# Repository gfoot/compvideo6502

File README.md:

# Composite/component video controller for homebrew 6502 computers

<table>
  <tr><td rowspan="2"></td><td></td></tr>
  <tr><td></td></tr>
</table>

This is my second iteration video output circuit for homebrew 6502 computers.  It's designed to work in a way that's fairly close to
how early 80s microcomputers tended to work, which means RAM shared between CPU and video controller, as this tends to provide the
fastest possible access for the CPU to the video memory.

In this second iteration, the main change from V1 is that the timings are easily configurable, allowing it to support NTSC as well
as PAL with just a few jumper changes, as well as non-standard sync timings if you want to experiment; and the image placement and
size is also easily configurable.

You can also use interlacing to double the vertical resolution to 512 pixels, and if you swap the clock crystal and adjust some
other timings, you can double the horizontal resolution as well.

More involved, higher clock frequencies and maybe more counters would also allow HD resolutions such as 720p and 1080i, though I
haven't tried those yet, and VGA if you also change the output layer to output plain RGB.

The limiting factor at these higher resolutions becomes memory - 384x256x2 already uses nearly half of the RAM.  I'm considering
addressing this through a banking scheme in an upcoming V3.

# Project contents

This project contains:
* Full KiCad schematics for the new design (<a href="images/compvideo6502_schematic.pdf">also available in PDF format</a>)
* A "PCB" layout that represents how you could build this on an array of five breadboards

This includes the 6502, RAM, ROM, oscillator, reset circuit, and address decoding circuits, along 
with the video controller.  If you're already happy with the way you're doing those in an existing system then you could mostly 
keep your old design instead, but the RAM and clock need to be integrated here, in order to be shared with the video controller.

# Next steps and expansion ideas

There are a few things I plan to do next, and I'm not sure what the order will be.  Feedback/contributions welcome - let me know 
if you try these or have other ideas!

* Upload some OS code - I have the code from my previous iteration which should work pretty well
* Document and explain it, maybe make a step-by-step build-and-test guide, video tutorial, or something like that
* Make some games for it!  That was the whole point really, having a video output circuit that's fast enough to support 
the kinds of game I grew up playing
* Colour output - using component video, pretty simple to add
* Higher resolutions?  Doubling the horizontal resolution is possible with the right pixel frequency (13.5MHz instead
of 16MHz) - and doubling the vertical resolution also works fine through interlacing.  Component video can also go up to 1080i I 
think, but can't find good specs on the sync frequencies for that.
* VGA output?  It's fairly similar, just higher frequency - but may be possible by swapping the crystal and adjusting the timings.  
It's why I wanted to make this more configurable than my first one.
* Planar video memory, as used on EGA and VGA graphics cards on PCs - I've always found it an interesting architecture, and it 
seems like a good way to implement colour output without needing faster memory
* Software control over the timing registers would be very neat and not very hard to do

# Caveats

The output impedance isn't exactly what it's meant to be, but it's close enough I think.

The 16MHz base frequency is what the BBC Micro used back in the day, but I think in the digital age the standard pixel sampling 
frequency for SDTV is 13.5MHz.  As a result, on an LCD display you get blurring and moire effects at 8MHz; and at 16MHz you lose 
most of the pixel detail completely.  I think with a 13.5MHz base frequency the picture would be sharper overall.

My first iteration output correct pre- and post-vsync equalization pulses, and serrations during the vsync; I left that out this 
time around as it doesn't seem to be necessary these days.  Maybe I'm missing something though.  As far as I can tell chips like 
the 6845 never supported this anyway - at least it's not mentioned in the datasheets.  So I'm guessing that since at least the 
1980s nobody has bothered with them.

I haven't worked out interlacing yet.  Websites say that you can turn it off with the right combination of sync pulses, but my TV
always says it's interlaced, so either I'm doing it wrong, or the TV just never says "576p" anyway.  The design here is
intentionally fully-interlaced, which might lead to increased vertical resolution in the end.  It should be possible to uninterlace
it with a small change to the sync timings.  Actually I suspect that this is becase composite doesn't support progressive scan -
with component video the non-interlaced mode might work better.

I used a lot of 74HCT40103s in this design - they're incredibly useful, and were fundamental to the simplification and tweakability 
of the timings in this design.  However it seems they might be harder to find online than other chips I tend to use - I had to 
order a second batch, and it was harder to find them this time around.  So maybe it wasn't the best choice...  It's possible to use 
74HCT163s instead, but you'll need more of them as they're only 4-bit counters.

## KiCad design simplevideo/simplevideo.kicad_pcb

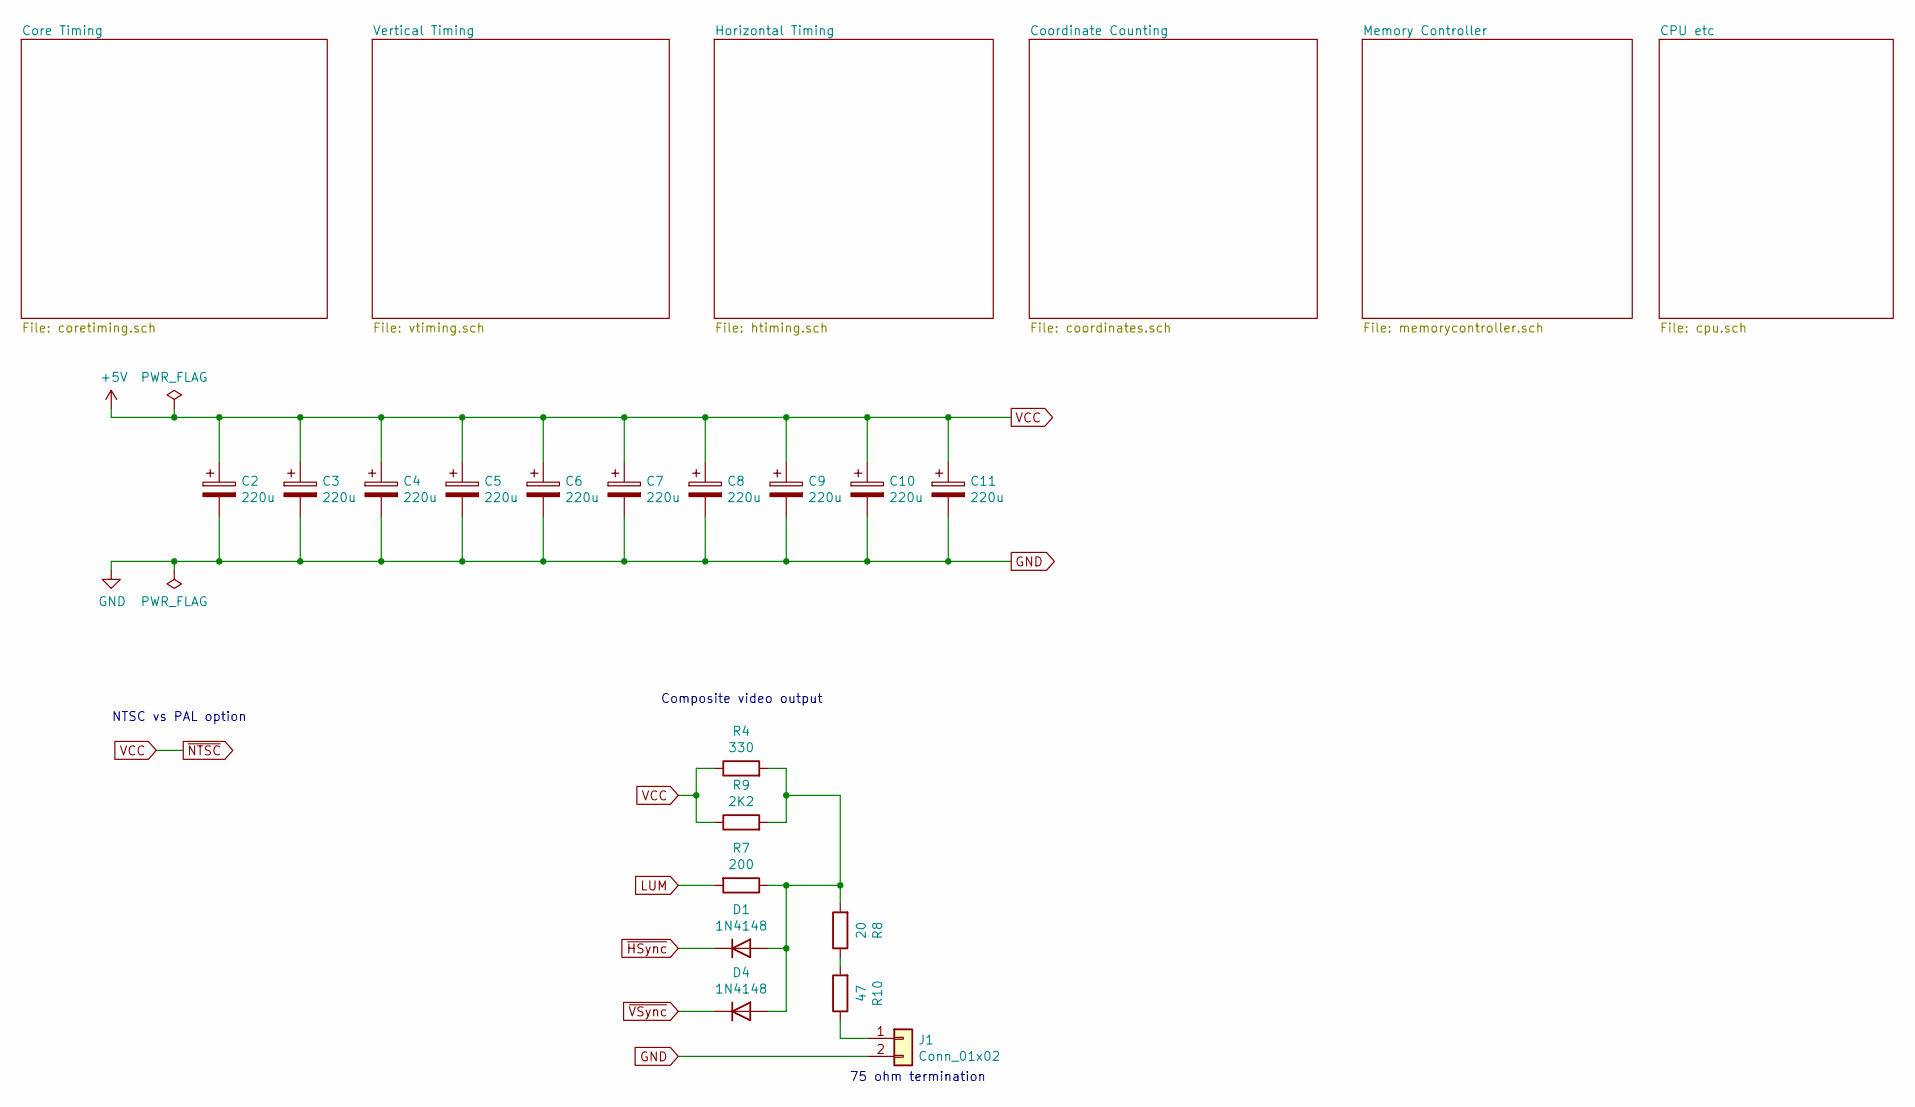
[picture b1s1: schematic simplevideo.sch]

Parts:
C2, C3, C4, C5, C6, C7, C8, C9, C10, C11: 220u; CP_Radial_D5.0mm_P2.50mm
D1, D4: 1N4148; D_DO-34_SOD68_P7.62mm_Horizontal
J1: Conn_01x02; PinHeader_1x02_P2.54mm_Vertical
R4: 330; R_Axial_DIN0204_L3.6mm_D1.6mm_P7.62mm_Horizontal
R7: 200; R_Axial_DIN0204_L3.6mm_D1.6mm_P7.62mm_Horizontal
R8: 20; R_Axial_DIN0204_L3.6mm_D1.6mm_P7.62mm_Horizontal
R9: 2K2; R_Axial_DIN0204_L3.6mm_D1.6mm_P7.62mm_Horizontal
R10: 47; R_Axial_DIN0204_L3.6mm_D1.6mm_P7.62mm_Horizontal

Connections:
GND: C2.2, C3.2, C4.2, C5.2, C6.2, C7.2, C8.2, C9.2, C10.2, C11.2, J1.2; also elsewhere on the board
LUM: R7.2; also elsewhere on the board
unnamed: D1.2 (A), D4.2 (A), R4.2, R7.1, R8.2, R9.2
unnamed: J1.1, R10.1
unnamed: R8.1, R10.2
VCC: C2.1, C3.1, C4.1, C5.1, C6.1, C7.1, C8.1, C9.1, C10.1, C11.1, R4.1, R9.1; also elsewhere on the board
~HSync: D1.1 (K); also elsewhere on the board
~VSync: D4.1 (K); also elsewhere on the board

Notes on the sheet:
NTSC vs PAL option
Composite video output
75 ohm termination

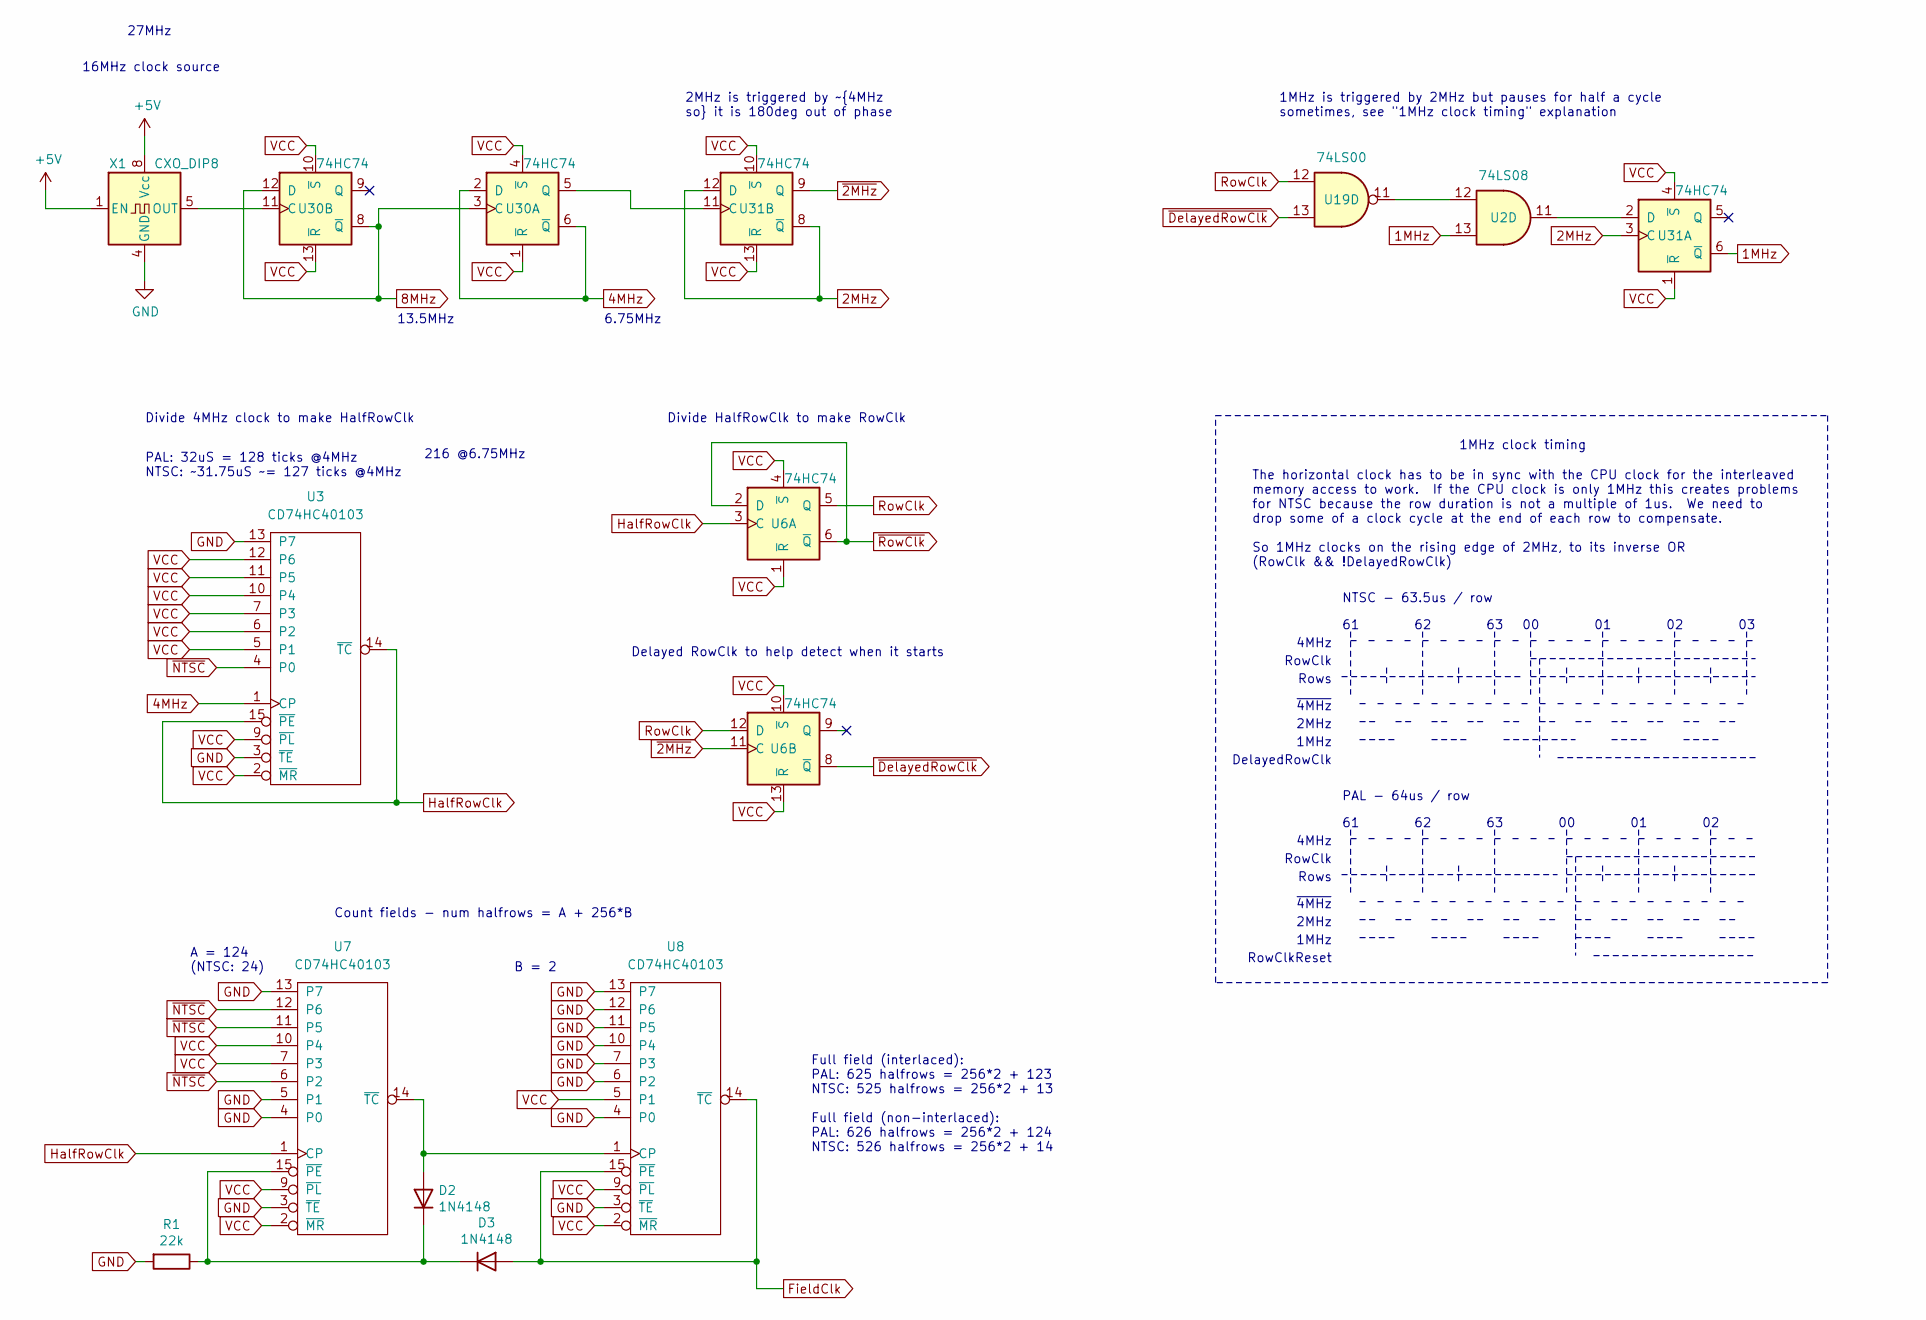
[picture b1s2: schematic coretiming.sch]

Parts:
D2, D3: 1N4148; D_DO-34_SOD68_P7.62mm_Horizontal
R1: 22k; R_Axial_DIN0204_L3.6mm_D1.6mm_P7.62mm_Horizontal
U2: 74LS08; DIP-14_W7.62mm
U3, U7, U8: CD74HC40103; DIP-16_W7.62mm
U6, U30, U31: 74HC74; DIP-14_W7.62mm
U19: 74LS00; DIP-14_W7.62mm
X1: CXO_DIP8; Oscillator_DIP-8

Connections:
1MHz: U2.13, U31.6 (~Q); also elsewhere on the board
2MHz: U31.3 (C), U31.8 (~Q), U31.12 (D)
4MHz: U3.1 (CP), U30.2 (D), U30.6 (~Q); also elsewhere on the board
8MHz: U30.3 (C), U30.8 (~Q), U30.12 (D); also elsewhere on the board
FieldClk: D3.2 (A), U8.14 (~TC), U8.15 (~PE); also elsewhere on the board
GND: R1.2, U3.3 (~TE), U3.8 (GND), U3.13 (P7), U7.3 (~TE), U7.4 (P0), U7.5 (P1), U7.8 (GND), U7.13 (P7), U8.3 (~TE), U8.4 (P0), U8.6 (P2), U8.7 (P3), U8.8 (GND), U8.10 (P4), U8.11 (P5), U8.12 (P6), U8.13 (P7), X1.4 (GND); also elsewhere on the board
HalfRowClk: U3.14 (~TC), U3.15 (~PE), U6.3 (C), U7.1 (CP); also elsewhere on the board
unnamed: D2.1 (K), D3.1 (K), R1.1, U7.15 (~PE)
unnamed: D2.2 (A), U7.14 (~TC), U8.1 (CP)
unnamed: U2.11, U31.2 (D)
unnamed: U2.12, U19.11
unnamed: U30.5 (Q), U31.11 (C)
unnamed: U30.11 (C), X1.5 (OUT)
RowClk: U6.5 (Q), U6.12 (D), U19.12; also elsewhere on the board
VCC: U3.2 (~MR), U3.4 (P0), U3.5 (P1), U3.6 (P2), U3.7 (P3), U3.9 (~PL), U3.10 (P4), U3.11 (P5), U3.12 (P6), U3.16 (VCC), U6.1 (~R), U6.4 (~S), U6.10 (~S), U6.13 (~R), U7.2 (~MR), U7.6 (P2), U7.7 (P3), U7.9 (~PL), U7.10 (P4), U7.11 (P5), U7.12 (P6), U7.16 (VCC), U8.2 (~MR), U8.5 (P1), U8.9 (~PL), U8.16 (VCC), U30.1 (~R), U30.4 (~S), U30.10 (~S), U30.13 (~R), U31.1 (~R), U31.4 (~S), U31.10 (~S), U31.13 (~R), X1.1 (EN), X1.8 (Vcc); also elsewhere on the board
~2MHz: U6.11 (C), U31.9 (Q); also elsewhere on the board
~DelayedRowClk: U6.8 (~Q), U19.13
~RowClk: U6.2 (D), U6.6 (~Q)

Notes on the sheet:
PAL: 32uS = 128 ticks @4MHz NTSC: ~~31.75uS ~~= 127 ticks @4MHz
Divide 4MHz clock to make HalfRowClk
Divide HalfRowClk to make RowClk
Full field (interlaced): PAL: 625 halfrows = 256*2 + 123 NTSC: 525 halfrows = 256*2 + 13 Full field (non-interlaced): PAL: 626 halfrows = 256*2 + 124 NTSC: 526 halfrows = 256*2 + 14
16MHz clock source
Count fields - num halfrows = A + 256*B
A = 124 (NTSC: 24)
B = 2
The horizontal clock has to be in sync with the CPU clock for the interleaved memory access to work. If the CPU clock is only 1MHz this creates problems for NTSC because the row duration is not a multiple of 1us. We need to drop some of a clock cycle at the end of each row to compensate. So 1MHz cl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
1MHz
2MHz
~4MHz
Rows
RowClk
4MHz
RowClkReset
NTSC - 63.5us / row
PAL - 64us / row
DelayedRowClk
1MHz clock timing
2MHz is triggered by ~4MHz so it is 180deg out of phase
1MHz is triggered by 2MHz but pauses for half a cycle sometimes, see "1MHz clock timing" explanation
Delayed RowClk to help detect when it starts
27MHz
13.5MHz
6.75MHz
216 @6.75MHz

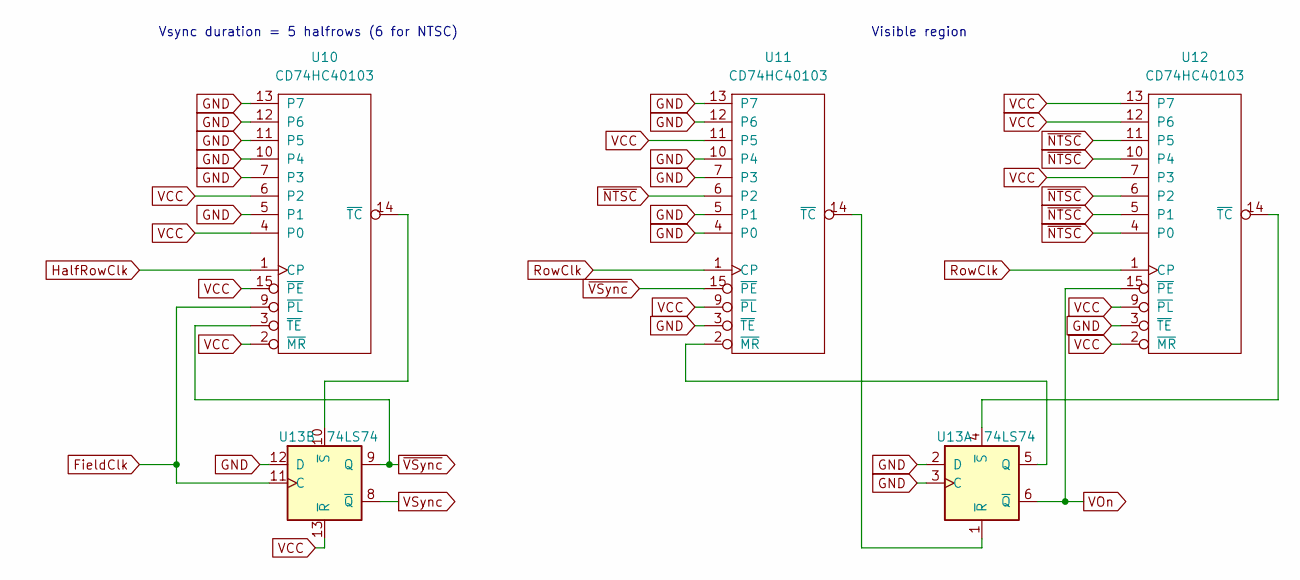
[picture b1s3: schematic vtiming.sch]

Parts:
U10, U11, U12: CD74HC40103; DIP-16_W7.62mm
U13: 74LS74; DIP-14_W7.62mm

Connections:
FieldClk: U10.9 (~PL), U13.11 (C); also elsewhere on the board
GND: U10.5 (P1), U10.7 (P3), U10.8 (GND), U10.10 (P4), U10.11 (P5), U10.12 (P6), U10.13 (P7), U11.3 (~TE), U11.4 (P0), U11.5 (P1), U11.7 (P3), U11.8 (GND), U11.10 (P4), U11.12 (P6), U11.13 (P7), U12.3 (~TE), U12.8 (GND), U13.2 (D), U13.3 (C), U13.12 (D); also elsewhere on the board
HalfRowClk: U10.1 (CP); also elsewhere on the board
unnamed: U10.14 (~TC), U13.10 (~S)
unnamed: U11.2 (~MR), U13.5 (Q)
unnamed: U11.14 (~TC), U13.1 (~R)
unnamed: U12.14 (~TC), U13.4 (~S)
RowClk: U11.1 (CP), U12.1 (CP); also elsewhere on the board
VCC: U10.2 (~MR), U10.4 (P0), U10.6 (P2), U10.15 (~PE), U10.16 (VCC), U11.6 (P2), U11.9 (~PL), U11.11 (P5), U11.16 (VCC), U12.2 (~MR), U12.4 (P0), U12.5 (P1), U12.6 (P2), U12.7 (P3), U12.9 (~PL), U12.10 (P4), U12.11 (P5), U12.12 (P6), U12.13 (P7), U12.16 (VCC), U13.13 (~R); also elsewhere on the board
VOn: U12.15 (~PE), U13.6 (~Q); also elsewhere on the board
VSync: U13.8 (~Q); also elsewhere on the board
~VSync: U10.3 (~TE), U11.15 (~PE), U13.9 (Q); also elsewhere on the board

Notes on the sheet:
Vsync duration = 5 halfrows (6 for NTSC)
Visible region

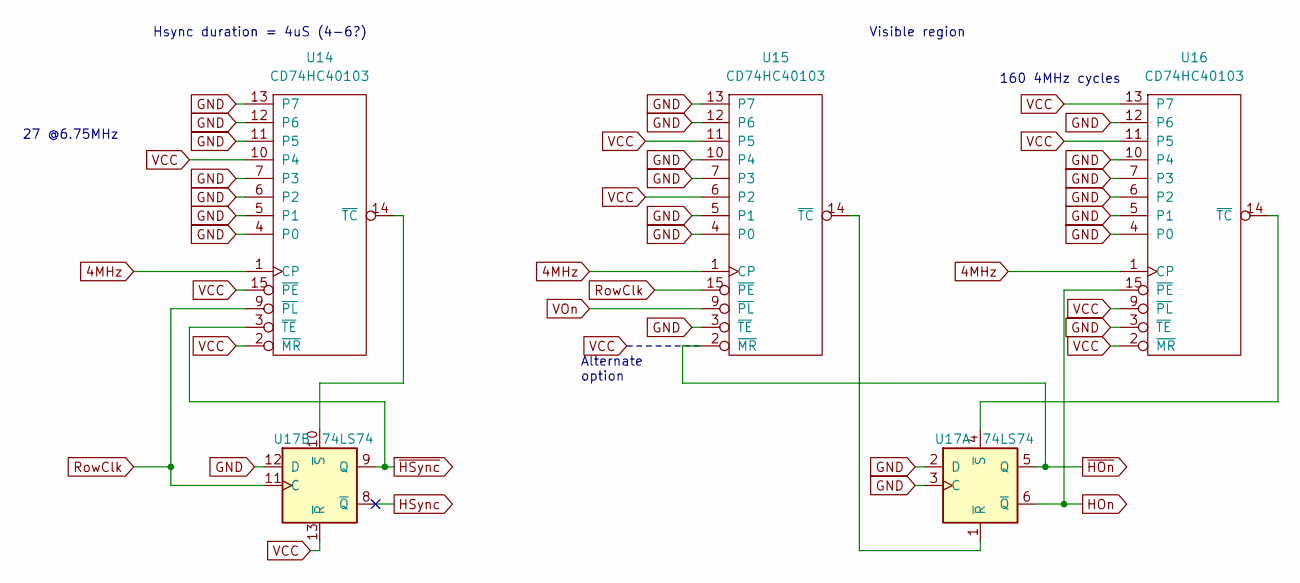
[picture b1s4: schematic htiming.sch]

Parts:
U14, U15, U16: CD74HC40103; DIP-16_W7.62mm
U17: 74LS74; DIP-14_W7.62mm

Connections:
4MHz: U14.1 (CP), U15.1 (CP), U16.1 (CP); also elsewhere on the board
GND: U14.4 (P0), U14.5 (P1), U14.6 (P2), U14.7 (P3), U14.8 (GND), U14.11 (P5), U14.12 (P6), U14.13 (P7), U15.3 (~TE), U15.4 (P0), U15.5 (P1), U15.7 (P3), U15.8 (GND), U15.10 (P4), U15.12 (P6), U15.13 (P7), U16.3 (~TE), U16.4 (P0), U16.5 (P1), U16.6 (P2), U16.7 (P3), U16.8 (GND), U16.10 (P4), U16.12 (P6), U17.2 (D), U17.3 (C), U17.12 (D); also elsewhere on the board
HOn: U16.15 (~PE), U17.6 (~Q); also elsewhere on the board
HSync: U17.8 (~Q)
unnamed: U14.14 (~TC), U17.10 (~S)
unnamed: U15.14 (~TC), U17.1 (~R)
unnamed: U16.14 (~TC), U17.4 (~S)
RowClk: U14.9 (~PL), U15.15 (~PE), U17.11 (C); also elsewhere on the board
VCC: U14.2 (~MR), U14.10 (P4), U14.15 (~PE), U14.16 (VCC), U15.6 (P2), U15.11 (P5), U15.16 (VCC), U16.2 (~MR), U16.9 (~PL), U16.11 (P5), U16.13 (P7), U16.16 (VCC), U17.13 (~R); also elsewhere on the board
VOn: U15.9 (~PL); also elsewhere on the board
~HOn: U15.2 (~MR), U17.5 (Q); also elsewhere on the board
~HSync: U14.3 (~TE), U17.9 (Q); also elsewhere on the board

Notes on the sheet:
Hsync duration = 4uS (4-6?)
Visible region
Alternate option
27 @6.75MHz
160 4MHz cycles

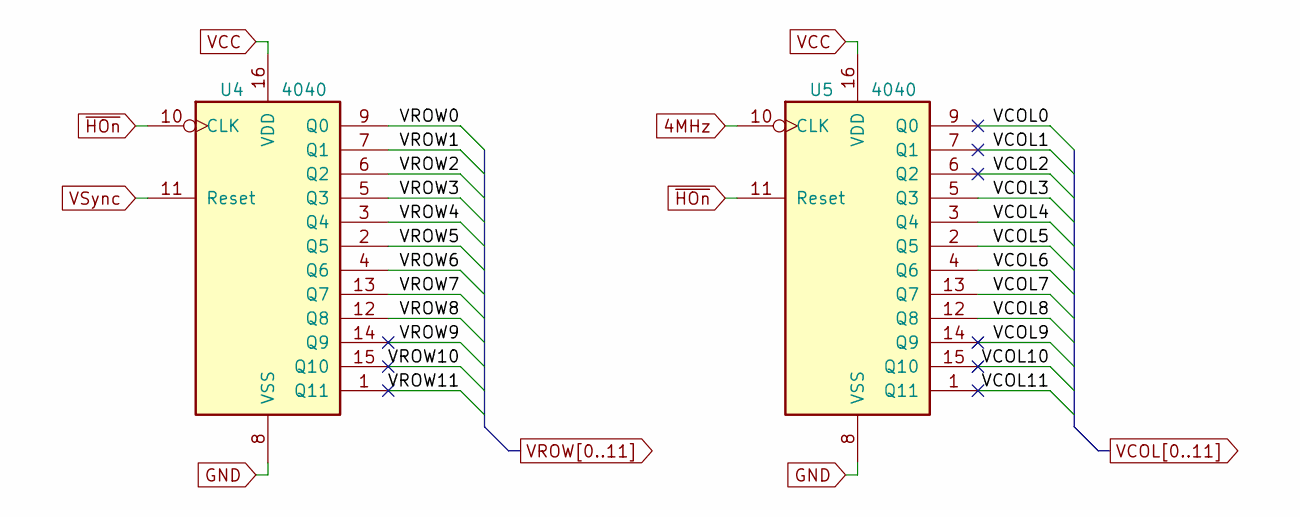
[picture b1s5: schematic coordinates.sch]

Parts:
U4, U5: 4040; DIP-16_W7.62mm

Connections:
4MHz: U5.10 (CLK); also elsewhere on the board
GND: U4.8 (VSS), U5.8 (VSS); also elsewhere on the board
VCC: U4.16 (VDD), U5.16 (VDD); also elsewhere on the board
VCOL0: U5.9 (Q0)
VCOL1: U5.7 (Q1)
VCOL2: U5.6 (Q2)
VCOL3: U5.5 (Q3); also elsewhere on the board
VCOL4: U5.3 (Q4); also elsewhere on the board
VCOL5: U5.2 (Q5); also elsewhere on the board
VCOL6: U5.4 (Q6); also elsewhere on the board
VCOL7: U5.13 (Q7); also elsewhere on the board
VCOL8: U5.12 (Q8); also elsewhere on the board
VCOL9: U5.14 (Q9)
VCOL10: U5.15 (Q10)
VCOL11: U5.1 (Q11)
VROW0: U4.9 (Q0); also elsewhere on the board
VROW1: U4.7 (Q1); also elsewhere on the board
VROW2: U4.6 (Q2); also elsewhere on the board
VROW3: U4.5 (Q3); also elsewhere on the board
VROW4: U4.3 (Q4); also elsewhere on the board
VROW5: U4.2 (Q5); also elsewhere on the board
VROW6: U4.4 (Q6); also elsewhere on the board
VROW7: U4.13 (Q7); also elsewhere on the board
VROW8: U4.12 (Q8); also elsewhere on the board
VROW9: U4.14 (Q9)
VROW10: U4.15 (Q10)
VROW11: U4.1 (Q11)
VSync: U4.11 (Reset); also elsewhere on the board
~HOn: U4.10 (CLK), U5.11 (Reset); also elsewhere on the board

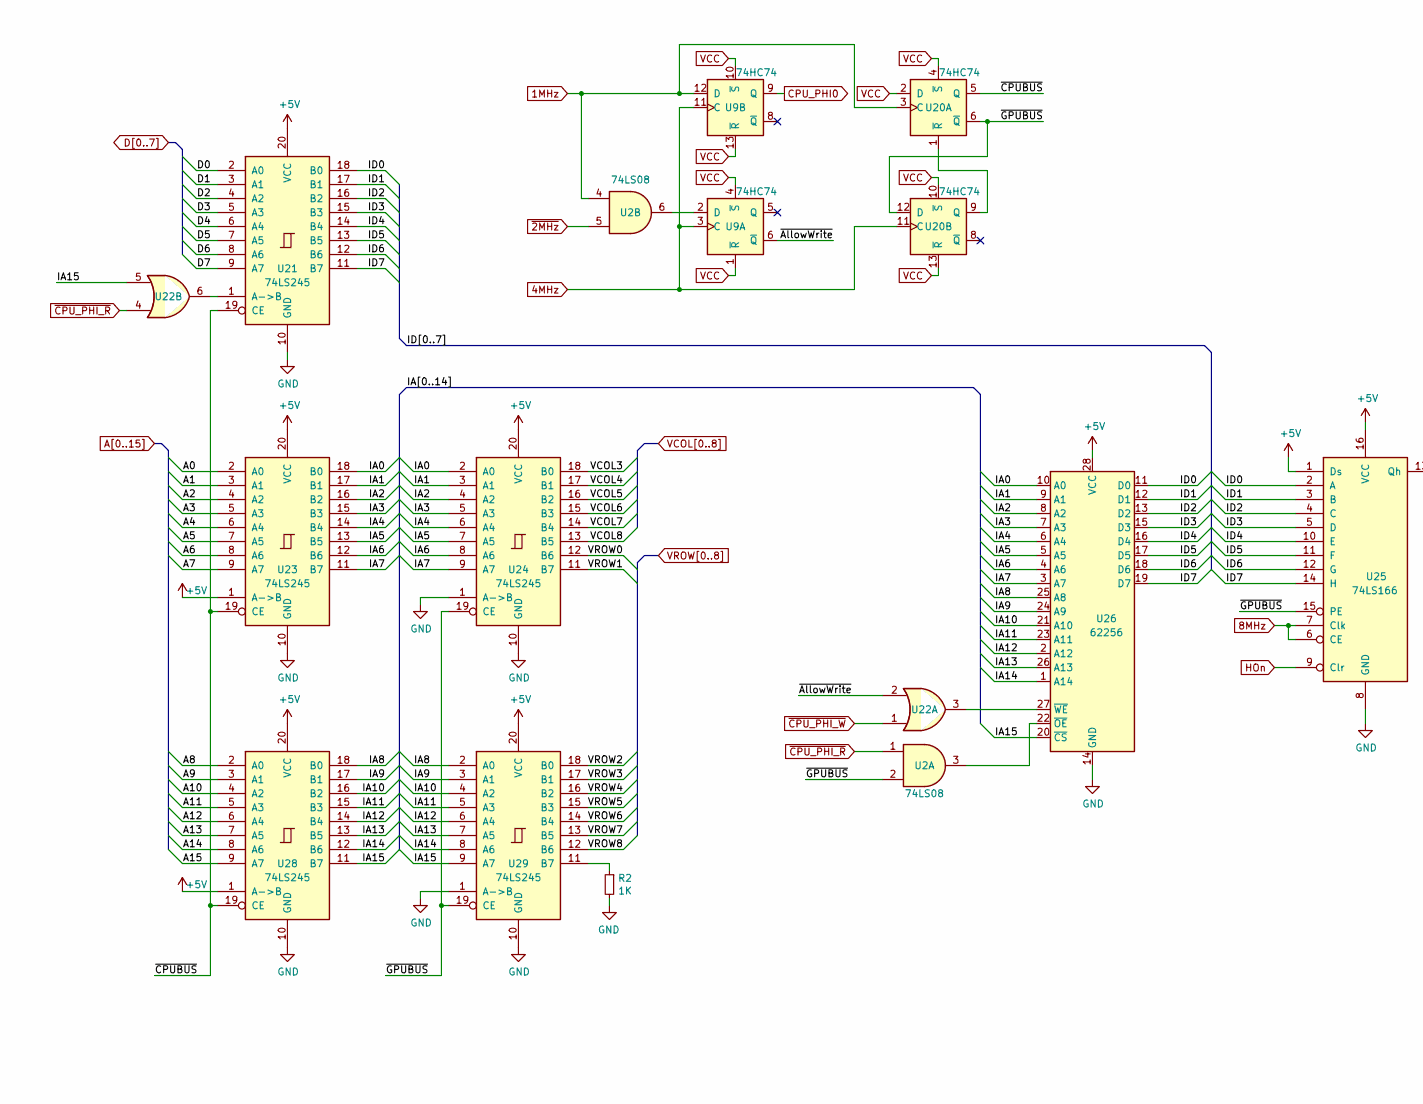
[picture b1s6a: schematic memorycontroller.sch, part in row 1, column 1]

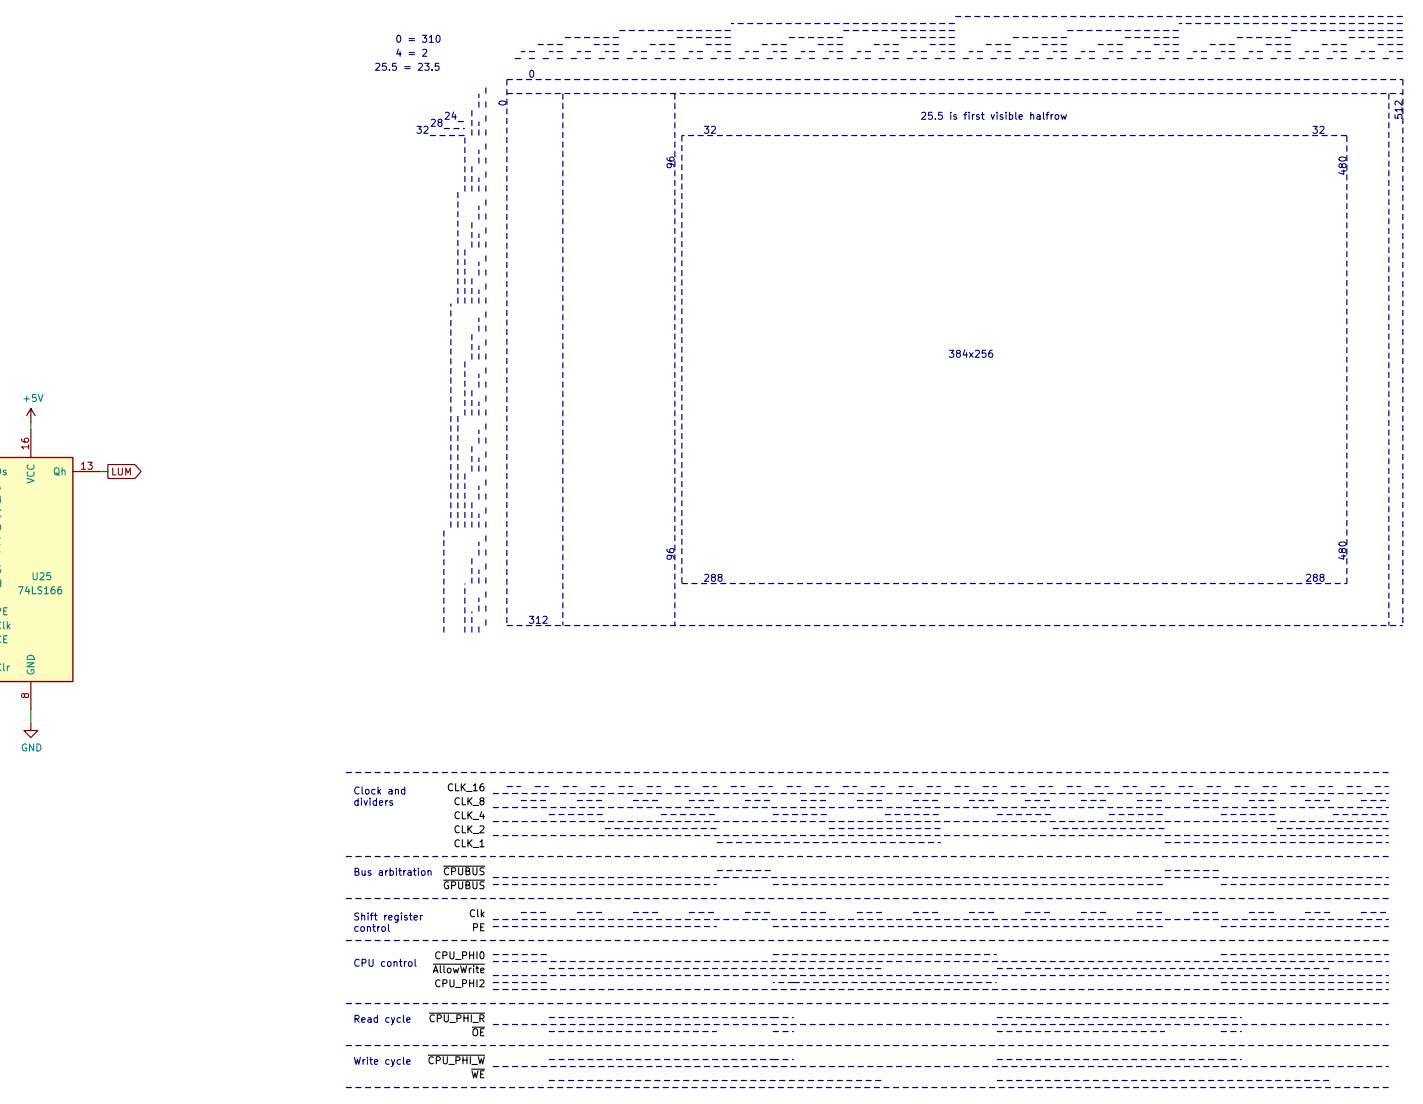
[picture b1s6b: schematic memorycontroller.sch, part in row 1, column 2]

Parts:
R2: 1K; R_Axial_DIN0207_L6.3mm_D2.5mm_P7.62mm_Horizontal
U2: 74LS08; DIP-14_W7.62mm
U9, U20: 74HC74; DIP-14_W7.62mm
U21, U23, U24, U28, U29: 74LS245; DIP-20_W7.62mm
U22: 74LS32; DIP-14_W7.62mm
U25: 74LS166; DIP-16_W7.62mm
U26: 62256; DIP-28_W15.24mm

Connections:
1MHz: U2.4, U9.12 (D), U20.3 (C); also elsewhere on the board
4MHz: U9.3 (C), U9.11 (C), U20.11 (C); also elsewhere on the board
8MHz: U25.6 (CE), U25.7 (Clk); also elsewhere on the board
/Memory Controller/IA0: U23.18 (B0), U24.2 (A0), U26.10 (A0)
/Memory Controller/IA1: U23.17 (B1), U24.3 (A1), U26.9 (A1)
/Memory Controller/IA2: U23.16 (B2), U24.4 (A2), U26.8 (A2)
/Memory Controller/IA3: U23.15 (B3), U24.5 (A3), U26.7 (A3)
/Memory Controller/IA4: U23.14 (B4), U24.6 (A4), U26.6 (A4)
/Memory Controller/IA5: U23.13 (B5), U24.7 (A5), U26.5 (A5)
/Memory Controller/IA6: U23.12 (B6), U24.8 (A6), U26.4 (A6)
/Memory Controller/IA7: U23.11 (B7), U24.9 (A7), U26.3 (A7)
/Memory Controller/IA8: U26.25 (A8), U28.18 (B0), U29.2 (A0)
/Memory Controller/IA9: U26.24 (A9), U28.17 (B1), U29.3 (A1)
/Memory Controller/IA10: U26.21 (A10), U28.16 (B2), U29.4 (A2)
/Memory Controller/IA11: U26.23 (A11), U28.15 (B3), U29.5 (A3)
/Memory Controller/IA12: U26.2 (A12), U28.14 (B4), U29.6 (A4)
/Memory Controller/IA13: U26.26 (A13), U28.13 (B5), U29.7 (A5)
/Memory Controller/IA14: U26.1 (A14), U28.12 (B6), U29.8 (A6)
/Memory Controller/IA15: U22.5, U26.20 (~CS), U28.11 (B7), U29.9 (A7)
/Memory Controller/ID0: U21.18 (B0), U25.2 (A), U26.11 (D0)
/Memory Controller/ID1: U21.17 (B1), U25.3 (B), U26.12 (D1)
/Memory Controller/ID2: U21.16 (B2), U25.4 (C), U26.13 (D2)
/Memory Controller/ID3: U21.15 (B3), U25.5 (D), U26.15 (D3)
/Memory Controller/ID4: U21.14 (B4), U25.10 (E), U26.16 (D4)
/Memory Controller/ID5: U21.13 (B5), U25.11 (F), U26.17 (D5)
/Memory Controller/ID6: U21.12 (B6), U25.12 (G), U26.18 (D6)
/Memory Controller/ID7: U21.11 (B7), U25.14 (H), U26.19 (D7)
/Memory Controller/~AllowWrite: U9.6 (~Q), U22.2
/Memory Controller/~CPUBUS: U20.5 (Q), U21.19 (CE), U23.19 (CE), U28.19 (CE)
/Memory Controller/~GPUBUS: U2.2, U20.6 (~Q), U20.12 (D), U24.19 (CE), U25.15 (PE), U29.19 (CE)
A0: U23.2 (A0); also elsewhere on the board
A1: U23.3 (A1); also elsewhere on the board
A2: U23.4 (A2); also elsewhere on the board
A3: U23.5 (A3); also elsewhere on the board
A4: U23.6 (A4); also elsewhere on the board
A5: U23.7 (A5); also elsewhere on the board
A6: U23.8 (A6); also elsewhere on the board
A7: U23.9 (A7); also elsewhere on the board
A8: U28.2 (A0); also elsewhere on the board
A9: U28.3 (A1); also elsewhere on the board
A10: U28.4 (A2); also elsewhere on the board
A11: U28.5 (A3); also elsewhere on the board
A12: U28.6 (A4); also elsewhere on the board
A13: U28.7 (A5); also elsewhere on the board
A14: U28.8 (A6); also elsewhere on the board
A15: U28.9 (A7); also elsewhere on the board
CPU_PHI0: U9.9 (Q); also elsewhere on the board
D0: U21.2 (A0); also elsewhere on the board
D1: U21.3 (A1); also elsewhere on the board
D2: U21.4 (A2); also elsewhere on the board
D3: U21.5 (A3); also elsewhere on the board
D4: U21.6 (A4); also elsewhere on the board
D5: U21.7 (A5); also elsewhere on the board
D6: U21.8 (A6); also elsewhere on the board
D7: U21.9 (A7); also elsewhere on the board
GND: R2.2, U21.10 (GND), U23.10 (GND), U24.1 (A->B), U24.10 (GND), U25.8 (GND), U26.14 (GND), U28.10 (GND), U29.1 (A->B), U29.10 (GND); also elsewhere on the board
HOn: U25.9 (Clr); also elsewhere on the board
LUM: U25.13 (Qh); also elsewhere on the board
unnamed: R2.1, U29.11 (B7)
unnamed: U2.3, U26.22 (~OE)
unnamed: U2.6, U9.2 (D)
unnamed: U20.1 (~R), U20.9 (Q)
unnamed: U21.1 (A->B), U22.6
unnamed: U22.3, U26.27 (~WE)
VCC: U9.1 (~R), U9.4 (~S), U9.10 (~S), U9.13 (~R), U20.2 (D), U20.4 (~S), U20.10 (~S), U20.13 (~R), U21.20 (VCC), U23.1 (A->B), U23.20 (VCC), U24.20 (VCC), U25.1 (Ds), U25.16 (VCC), U26.28 (VCC), U28.1 (A->B), U28.20 (VCC), U29.20 (VCC); also elsewhere on the board
VCOL3: U24.18 (B0); also elsewhere on the board
VCOL4: U24.17 (B1); also elsewhere on the board
VCOL5: U24.16 (B2); also elsewhere on the board
VCOL6: U24.15 (B3); also elsewhere on the board
VCOL7: U24.14 (B4); also elsewhere on the board
VCOL8: U24.13 (B5); also elsewhere on the board
VROW0: U24.12 (B6); also elsewhere on the board
VROW1: U24.11 (B7); also elsewhere on the board
VROW2: U29.18 (B0); also elsewhere on the board
VROW3: U29.17 (B1); also elsewhere on the board
VROW4: U29.16 (B2); also elsewhere on the board
VROW5: U29.15 (B3); also elsewhere on the board
VROW6: U29.14 (B4); also elsewhere on the board
VROW7: U29.13 (B5); also elsewhere on the board
VROW8: U29.12 (B6); also elsewhere on the board
~2MHz: U2.5; also elsewhere on the board
~CPU_PHI_R: U2.1, U22.4; also elsewhere on the board
~CPU_PHI_W: U22.1; also elsewhere on the board

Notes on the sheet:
512
312
25.5 is first visible halfrow
0 = 310
4 = 2
25.5 = 23.5
480
288
384x256
Shift register control
CPU control
Read cycle
Write cycle
Clock and dividers
Bus arbitration

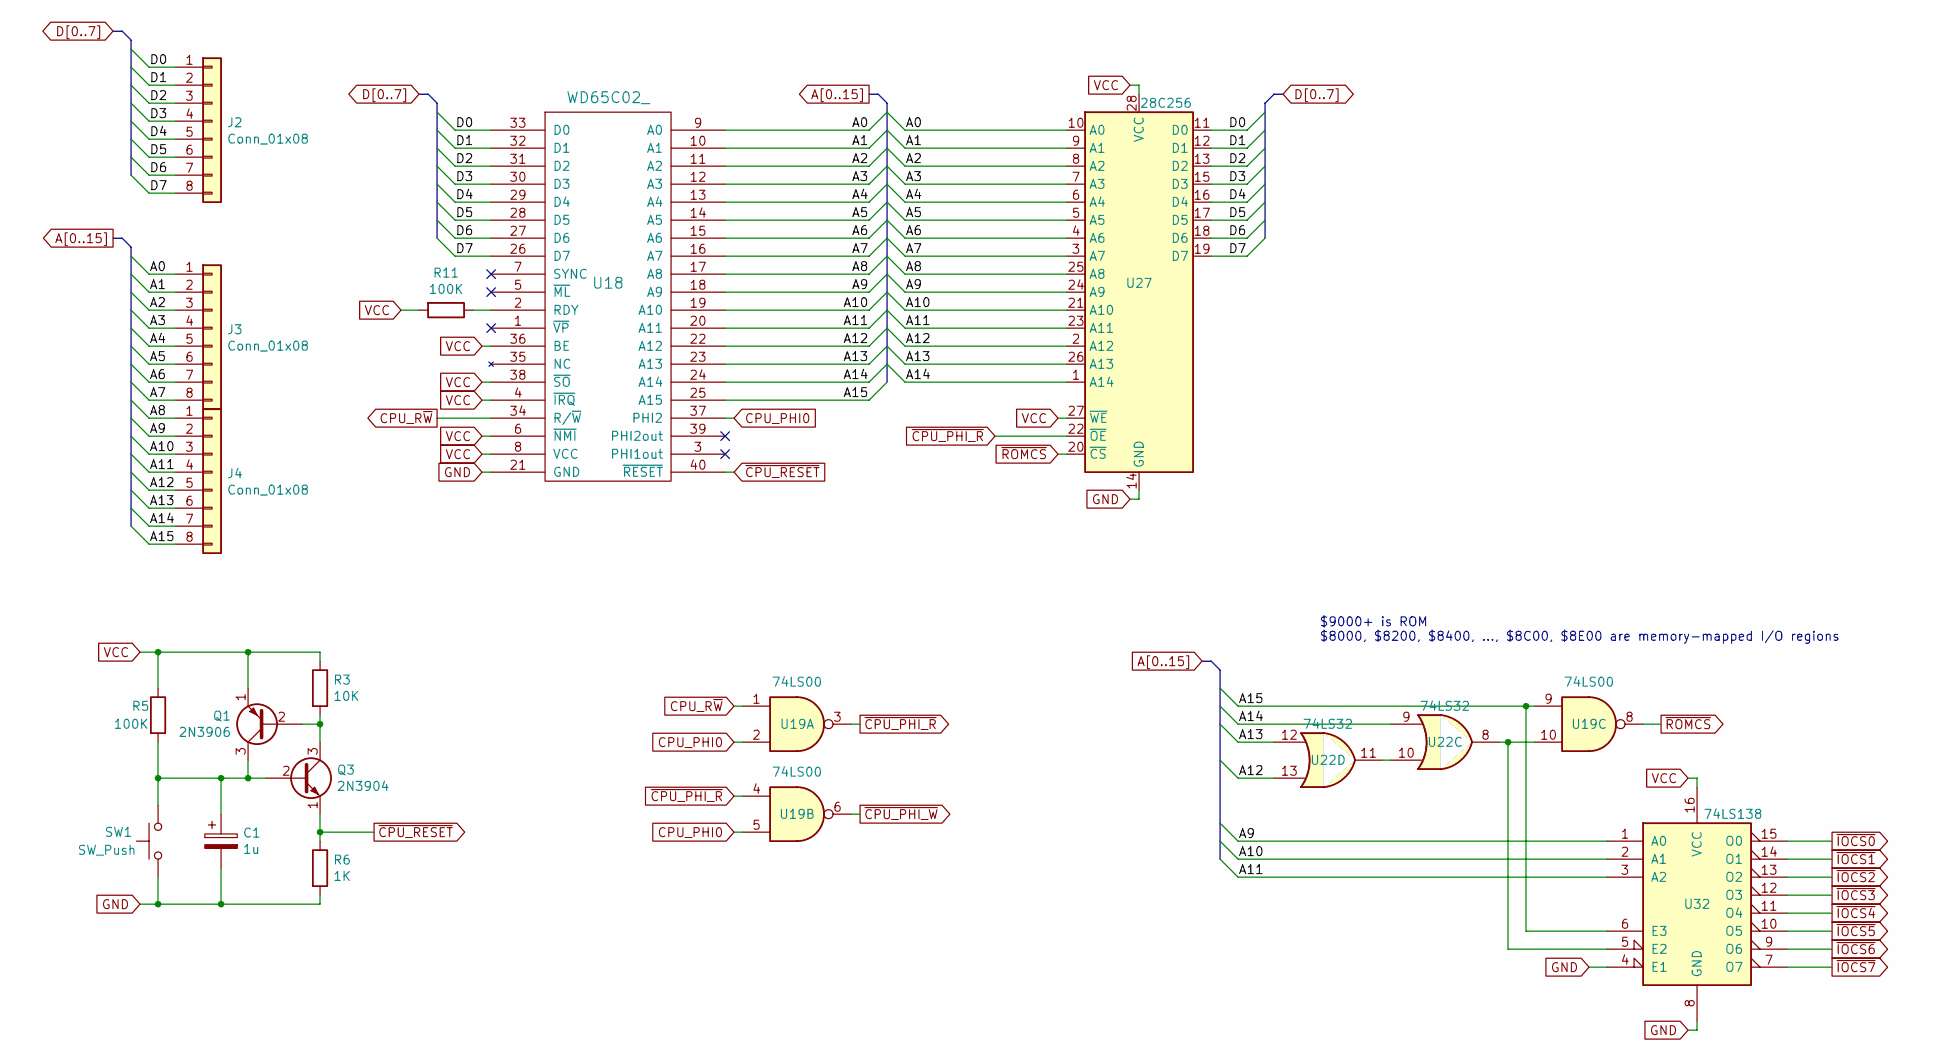
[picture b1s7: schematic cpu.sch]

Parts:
C1: 1u; CP_Radial_D5.0mm_P2.50mm
J2, J3, J4: Conn_01x08; PinHeader_1x08_P2.54mm_Vertical
Q1: 2N3906; TO-92_Inline
Q3: 2N3904; TO-92_Inline
R3: 10K; R_Axial_DIN0207_L6.3mm_D2.5mm_P7.62mm_Horizontal
R5, R11: 100K; R_Axial_DIN0207_L6.3mm_D2.5mm_P7.62mm_Horizontal
R6: 1K; R_Axial_DIN0207_L6.3mm_D2.5mm_P7.62mm_Horizontal
SW1: SW_Push; SW_PUSH_6mm
U18: WD65C02_; DIP-40_W15.24mm
U19: 74LS00; DIP-14_W7.62mm
U22: 74LS32; DIP-14_W7.62mm
U27: 28C256; DIP-28_W15.24mm
U32: 74LS138; DIP-16_W7.62mm

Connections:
A0: J3.1, U18.9 (A0), U27.10 (A0); also elsewhere on the board
A1: J3.2, U18.10 (A1), U27.9 (A1); also elsewhere on the board
A2: J3.3, U18.11 (A2), U27.8 (A2); also elsewhere on the board
A3: J3.4, U18.12 (A3), U27.7 (A3); also elsewhere on the board
A4: J3.5, U18.13 (A4), U27.6 (A4); also elsewhere on the board
A5: J3.6, U18.14 (A5), U27.5 (A5); also elsewhere on the board
A6: J3.7, U18.15 (A6), U27.4 (A6); also elsewhere on the board
A7: J3.8, U18.16 (A7), U27.3 (A7); also elsewhere on the board
A8: J4.1, U18.17 (A8), U27.25 (A8); also elsewhere on the board
A9: J4.2, U18.18 (A9), U27.24 (A9), U32.1 (A0); also elsewhere on the board
A10: J4.3, U18.19 (A10), U27.21 (A10), U32.2 (A1); also elsewhere on the board
A11: J4.4, U18.20 (A11), U27.23 (A11), U32.3 (A2); also elsewhere on the board
A12: J4.5, U18.22 (A12), U22.13, U27.2 (A12); also elsewhere on the board
A13: J4.6, U18.23 (A13), U22.12, U27.26 (A13); also elsewhere on the board
A14: J4.7, U18.24 (A14), U22.9, U27.1 (A14); also elsewhere on the board
A15: J4.8, U18.25 (A15), U19.9, U32.6 (E3); also elsewhere on the board
CPU_PHI0: U18.37 (PHI2), U19.2, U19.5; also elsewhere on the board
CPU_R~W: U18.34 (R/~W), U19.1
D0: J2.1, U18.33 (D0), U27.11 (D0); also elsewhere on the board
D1: J2.2, U18.32 (D1), U27.12 (D1); also elsewhere on the board
D2: J2.3, U18.31 (D2), U27.13 (D2); also elsewhere on the board
D3: J2.4, U18.30 (D3), U27.15 (D3); also elsewhere on the board
D4: J2.5, U18.29 (D4), U27.16 (D4); also elsewhere on the board
D5: J2.6, U18.28 (D5), U27.17 (D5); also elsewhere on the board
D6: J2.7, U18.27 (D6), U27.18 (D6); also elsewhere on the board
D7: J2.8, U18.26 (D7), U27.19 (D7); also elsewhere on the board
GND: C1.2, R6.2, SW1.1, U18.21 (GND), U27.14 (GND), U32.4 (E1), U32.8 (GND); also elsewhere on the board
unnamed: C1.1, Q1.3 (C), Q3.2 (B), R5.2, SW1.2
unnamed: Q1.2 (B), Q3.3 (C), R3.2
unnamed: R11.1, U18.2 (RDY)
unnamed: U19.10, U22.8, U32.5 (E2)
unnamed: U22.10, U22.11
VCC: Q1.1 (E), R3.1, R5.1, R11.2, U18.4 (~IRQ), U18.6 (~NMI), U18.8 (VCC), U18.36 (BE), U18.38 (~SO), U27.27 (~WE), U27.28 (VCC), U32.16 (VCC); also elsewhere on the board
~CPU_PHI_R: U19.3, U19.4, U27.22 (~OE); also elsewhere on the board
~CPU_PHI_W: U19.6; also elsewhere on the board
~CPU_RESET: Q3.1 (E), R6.1, U18.40 (~RESET)
~IOCS0: U32.15 (O0)
~IOCS1: U32.14 (O1)
~IOCS2: U32.13 (O2)
~IOCS3: U32.12 (O3)
~IOCS4: U32.11 (O4)
~IOCS5: U32.10 (O5)
~IOCS6: U32.9 (O6)
~IOCS7: U32.7 (O7)
~ROMCS: U19.8, U27.20 (~CS)

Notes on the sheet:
$9000+ is ROM $8000, $8200, $8400, ..., $8C00, $8E00 are memory-mapped I/O regions
